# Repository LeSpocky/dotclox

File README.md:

dotclox
=======

Build a [word clock](https://www.mikrocontroller.net/articles/Word_Clock)
out of a [DotBlox](https://wiki.blinkenarea.org/index.php/DotBloxEnglish) …

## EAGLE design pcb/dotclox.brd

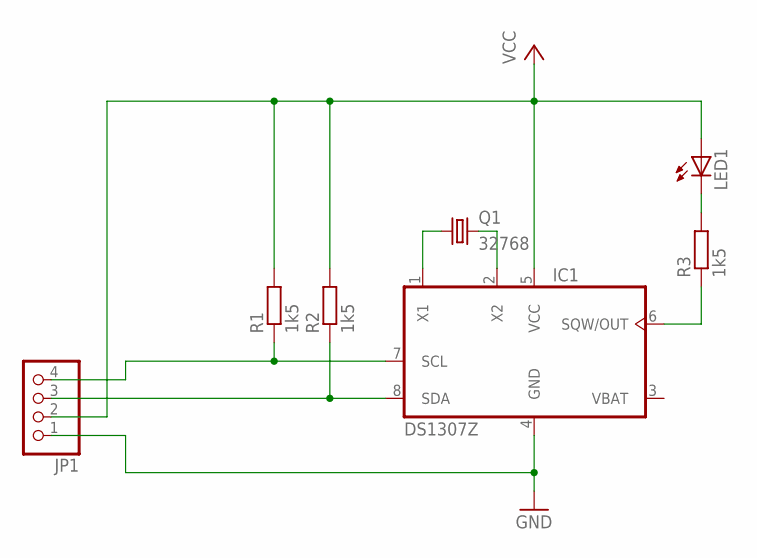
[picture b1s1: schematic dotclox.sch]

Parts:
IC1: DS1307Z; SO08
JP1: PINHD-1X4; 1X04
LED1: LED3MM
Q1: 32768; TC26H
R1, R2, R3: 1k5; R0603

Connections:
GND: IC1.4 (GND), JP1.1
unnamed: IC1.1 (X1), Q1.1
unnamed: IC1.2 (X2), Q1.2
unnamed: IC1.6 (SQW/OUT), R3.1
unnamed: LED1.K (C), R3.2
SCL: IC1.7 (SCL), JP1.4, R1.1
SDA: IC1.8 (SDA), JP1.3, R2.1
VBAT: IC1.3 (VBAT)
VCC: IC1.5 (VCC), JP1.2, LED1.A, R1.2, R2.2

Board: 2 copper layers, 11 parts (0 on the bottom side), 8 nets, no tracks yet.

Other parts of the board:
U$1, U$2, U$3, U$4: 3,2-PAD

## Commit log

2014-12-02 import dotblox pcb files
2014-12-02 start pcb
2014-12-02 fix board dimension and add GND polygon
2014-12-29 add front plate drawing stub and adapt README
2014-12-29 add grid for LEDs
2014-12-30 set letters
2014-12-30 pcb: update lib
2015-12-01 add some ressources
2015-12-01 add basic parts to sch and brd
